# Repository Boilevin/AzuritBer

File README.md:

# AzuritBer
Ardumower full odometry version
see https://www.ardumower.de  and https://wiki.ardumower.de/index.php?title=AzuritBer_Firmware_(English)# for more info.

Master branch need PCB1.3 or 1.4 ,ODOMETRY on drive motor and IMU : GY-521 / or GY-88  based on MPU6050 version

OPTIONAL:

        	RFID BOARD PN5180 AS RFID READER and ESP32 dev kit to manage SPI communication with PN5180 and WIFI/BT for arduremote
	
		RASPBERRY for vision or camera streaming:
	
See other branch for GY-87  or MPU-9250/9255 version

GY87 version use a GY87 IMU connected on I2C1 to avoid i2c adress conflit with RTC .

RL1000 version is the code for robomow rl model platform.
	The 3 big mow motor use 3 BTS7960 motor driver and 3 INA226 with R010 instead R100 to manage motor sense over I2C

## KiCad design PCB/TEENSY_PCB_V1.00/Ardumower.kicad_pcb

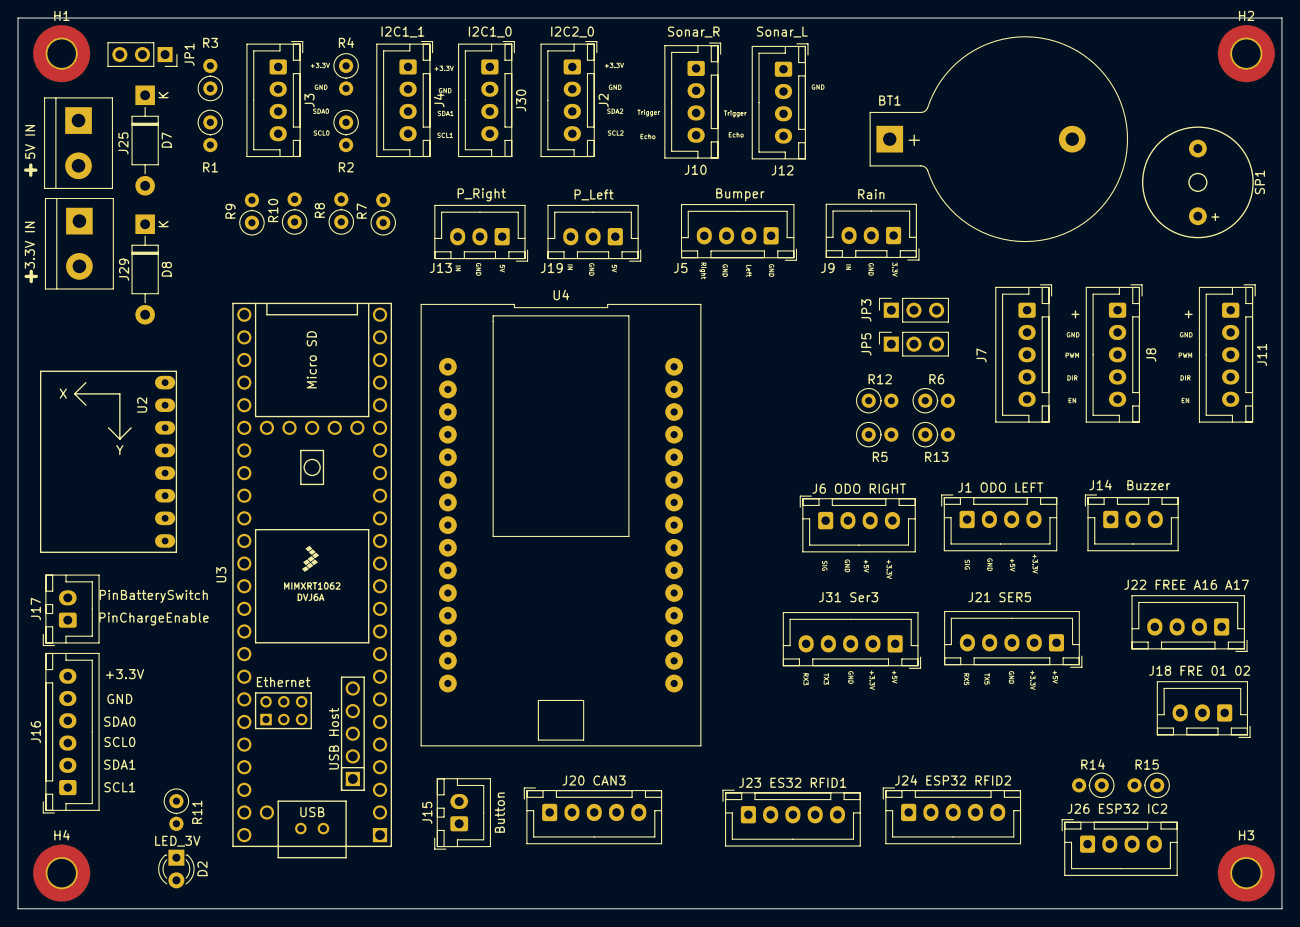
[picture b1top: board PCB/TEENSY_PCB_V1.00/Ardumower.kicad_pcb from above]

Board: 2 copper layers, 141.9 x 100.0 mm, 59 parts (0 on the bottom side), 66 nets, no tracks yet.

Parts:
BT1: Battery_Cell; BatteryHolder_Keystone_103_1x20mm
D2: LED_3V; LED_D3.0mm
D7, D8: 1N5819; D_DO-41_SOD81_P10.16mm_Horizontal
H1, H2, H3, H4: MountingHole_Pad; MountingHole_3.2mm_M3_Pad_TopBottom
J1 ODO LEFT: ODO_Left; JST_XH_B4B-XH-A_1x04_P2.50mm_Vertical
J2: I2C2_0; JST_XH_B4B-XH-A_1x04_P2.50mm_Vertical
J3: I2C0_0; JST_XH_B4B-XH-A_1x04_P2.50mm_Vertical
J4: I2C1_1; JST_XH_B4B-XH-A_1x04_P2.50mm_Vertical
J5: Bumper; JST_XH_B4B-XH-A_1x04_P2.50mm_Vertical
J6 ODO RIGHT: ODO_Right; JST_XH_B4B-XH-A_1x04_P2.50mm_Vertical
J7: Motor_Right1; JST_XH_B5B-XH-A_1x05_P2.50mm_Vertical
J8: Motor_Left1; JST_XH_B5B-XH-A_1x05_P2.50mm_Vertical
J9: Rain; JST_XH_B3B-XH-A_1x03_P2.50mm_Vertical
J10: Sonar_R; JST_XH_B4B-XH-A_1x04_P2.50mm_Vertical
J11: Cutter; JST_XH_B5B-XH-A_1x05_P2.50mm_Vertical
J12: Sonar_L; JST_XH_B4B-XH-A_1x04_P2.50mm_Vertical
J13: P_Right; JST_XH_B3B-XH-A_1x03_P2.50mm_Vertical
J14: Buzzer; JST_XH_B3B-XH-A_1x03_P2.50mm_Vertical
J15: Button; JST_XH_B2B-XH-A_1x02_P2.50mm_Vertical
J16: Power_PCB1; JST_XH_B6B-XH-A_1x06_P2.50mm_Vertical
J17: Power_PCB2; JST_XH_B2B-XH-A_1x02_P2.50mm_Vertical
J18 FRE 01 02: Free01_02; JST_XH_B3B-XH-A_1x03_P2.50mm_Vertical
J19: P_Left; JST_XH_B3B-XH-A_1x03_P2.50mm_Vertical
J20 CAN3: Can3; JST_XH_B5B-XH-A_1x05_P2.50mm_Vertical
J21 SER5: Ser5; JST_XH_B5B-XH-A_1x05_P2.50mm_Vertical
J22 FREE A16 A17: FreeA16_A17; JST_XH_B4B-XH-A_1x04_P2.50mm_Vertical
J23 ES32 RFID1: ESP RFID1; JST_XH_B5B-XH-A_1x05_P2.50mm_Vertical
J24 ESP32 RFID2: ESP RFID2; JST_XH_B5B-XH-A_1x05_P2.50mm_Vertical
J25: 5V IN; TerminalBlock_bornier-2_P5.08mm
J26 ESP32 IC2: ESP32 I2C; JST_XH_B4B-XH-A_1x04_P2.50mm_Vertical
J29: 3.3V IN; TerminalBlock_bornier-2_P5.08mm
J30: I2C1_0; JST_XH_B4B-XH-A_1x04_P2.50mm_Vertical
J31: Ser3; JST_XH_B5B-XH-A_1x05_P2.50mm_Vertical
JP1: Jumper_3.3V; PinSocket_1x03_P2.54mm_Vertical
JP3: MotorPower; PinSocket_1x03_P2.54mm_Vertical
JP5: CutterPower; PinSocket_1x03_P2.54mm_Vertical
R1, R3: XXXX; R_Axial_DIN0207_L6.3mm_D2.5mm_P2.54mm_Vertical
R2, R4, R14, R15: XXX; R_Axial_DIN0207_L6.3mm_D2.5mm_P2.54mm_Vertical
R5, R6, R7, R9: 1KO; R_Axial_DIN0207_L6.3mm_D2.5mm_P2.54mm_Vertical
R8, R10: 1.5KO; R_Axial_DIN0207_L6.3mm_D2.5mm_P2.54mm_Vertical
R11: 100; R_Axial_DIN0207_L6.3mm_D2.5mm_P2.54mm_Vertical
R12, R13: 1,5KO; R_Axial_DIN0207_L6.3mm_D2.5mm_P2.54mm_Vertical
SP1: SPEAKER; Buzzer_12x9.5RM7.6
U2: GY-521
U3: Teensy4.1; Teensy41
U4: ESP32-DEVKIT-V1

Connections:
+3V3: J1 ODO LEFT.4, J2.1, J3.1, J4.1, J6 ODO RIGHT.4, J9.1, J10.1, J12.1, J16.6, J20 CAN3.2, J21 SER5.2, J22 FREE A16 A17.1, J30.1, J31.2, JP1.2, JP3.3, JP5.3, R1.2, R2.2, R3.1, R4.2, R11.2, U2.1
+5V: D7.1, J1 ODO LEFT.3, J6 ODO RIGHT.3, J13.1, J14.1, J19.1, J20 CAN3.1, J21 SER5.1, J23 ES32 RFID1.2, J31.1, JP3.1, JP5.1, U3.48, U4.15
CRX3: J20 CAN3.5, U3.22
CTX3: J20 CAN3.4, U3.23
Free01: J18 FRE 01 02.2, U3.35
Free02: J18 FRE 01 02.3, U3.24
FreeA16: J22 FREE A16 A17.3, U3.32
FreeA17: J22 FREE A16 A17.4, U3.33
GND: BT1.2, D2.1, H1.1, H2.1, H3.1, H4.1, J1 ODO LEFT.2, J2.2, J3.2, J4.2, J5.1, J5.3, J6 ODO RIGHT.2, J7.2, J8.2, J9.2, J10.2, J11.2, J12.2, J13.2, J14.2, J15.1, J16.5, J18 FRE 01 02.1, J19.2, J20 CAN3.3, J21 SER5.3, J22 FREE A16 A17.2, J23 ES32 RFID1.1, J25.1, J26 ESP32 IC2.1, J29.1, J30.2, J31.3, R8.2, R10.2, R12.2, R13.2, SP1.1, U2.2, U3.47, U4.14
unnamed: BT1.1, U3.50
unnamed: D2.2, R11.1
unnamed: D7.2, J25.2
unnamed: D8.1, JP1.1
unnamed: D8.2, J29.2
unnamed: J1 ODO LEFT.1, R5.1, R12.1
unnamed: J6 ODO RIGHT.1, R6.1, R13.1
unnamed: J7.1, J8.1, JP3.2
unnamed: J11.1, JP5.2
unnamed: J13.3, R7.1, R8.1
unnamed: J19.3, R9.1, R10.1
unnamed: J23 ES32 RFID1.3, U4.13
unnamed: J23 ES32 RFID1.4, U4.12
unnamed: J23 ES32 RFID1.5, U4.11
unnamed: J24 ESP32 RFID2.1, U4.30
unnamed: J24 ESP32 RFID2.2, U4.25
unnamed: J24 ESP32 RFID2.3, U4.24
unnamed: J24 ESP32 RFID2.4, J26 ESP32 IC2.4, R14.1, R15.1, U4.16
unnamed: J26 ESP32 IC2.2, R14.2, U4.18
unnamed: J26 ESP32 IC2.3, R15.2, U4.20
unnamed: JP1.3, U3.46
RX1: U3.2, U4.22
RX3: J31.5, U3.37
RX5: J21 SER5.5, U3.43
SCL0: J3.4, J16.3, R1.1, U2.3, U3.41
SCL1: J4.4, J16.1, J30.4, R2.1, U3.38
SCL2: J2.4, U3.16
SDA0: J3.3, J16.4, R3.2, U2.4, U3.40
SDA1: J4.3, J16.2, J30.3, R4.1, U3.39
SDA2: J2.3, U3.17
TX1: U3.3, U4.21
TX3: J31.4, U3.36
TX5: J21 SER5.4, U3.42
pinBatterySwitch: J17.2, U3.25
pinBumperLeft: J5.4, U3.27
pinBumperRight: J5.2, U3.28
pinButton: J15.2, U3.30
pinBuzzer: J14.3, SP1.2, U3.29
pinChargeEnable: J17.1, U3.26
pinMotorLeftDir: J8.4, U3.8
pinMotorLeftEnable: J8.5, U3.7
pinMotorLeftPWM: J8.3, U3.9
pinMotorMowDir: J11.4, U3.11
pinMotorMowEnable: J11.5, U3.10
pinMotorMowPWM: J11.3, U3.12
pinMotorRightDir: J7.4, U3.5
pinMotorRightEnable: J7.5, U3.4
pinMotorRightPWM: J7.3, U3.6
pinOdometryLeft: R6.2, U3.14
pinOdometryRight: R5.2, U3.13
pinPerimeterLeft: R9.2, U3.45
pinPerimeterRight: R7.2, U3.44
pinRain: J9.3, U3.31
pinSonarLeftEcho: J12.4, U3.18
pinSonarLeftTrigger: J12.3, U3.20
pinSonarRightEcho: J10.4, U3.19
pinSonarRightTrigger: J10.3, U3.21

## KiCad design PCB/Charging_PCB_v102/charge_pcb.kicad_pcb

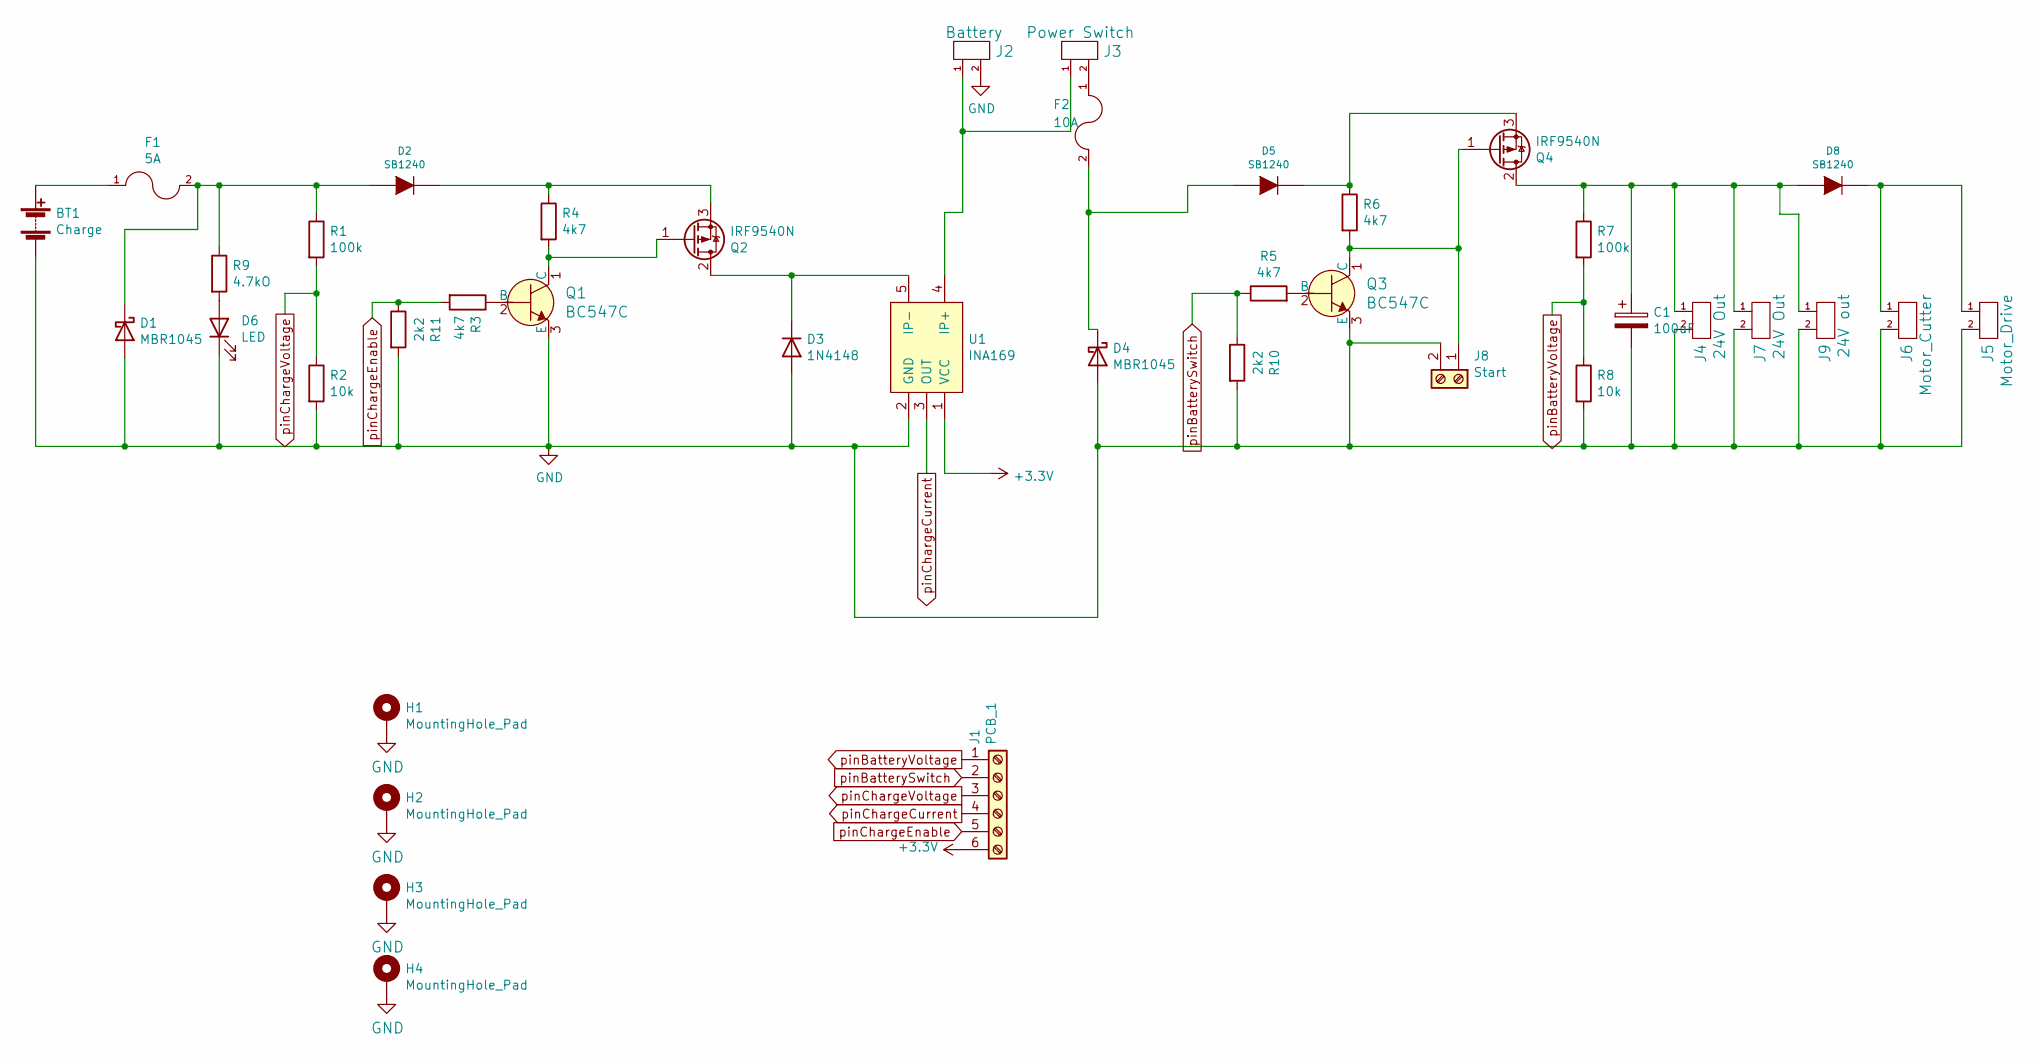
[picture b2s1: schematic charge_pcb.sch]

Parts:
BT1: Charge; Anschlussklemme_2P_RM5,08
C1: 100uF; Elko_vert_11.2x6.3mm_RM2.5
D1, D4: MBR1045; TO-220-2_Vertical
D2, D5, D8: SB1240; D_DO-41_SOD81_P10.16mm_Horizontal
D3: 1N4148; D_DO-35_SOD27_P7.62mm_Horizontal
D6: LED; LED_D1.8mm_W3.3mm_H2.4mm
F1: 5A; Fuseholder_Reichelt_PL112000
F2: 10A; Fuseholder_Reichelt_PL112000
H1, H2, H3, H4: MountingHole_Pad; MountingHole_3.2mm_M3_DIN965_Pad_TopBottom
J1: PCB_1; JST_XH_B6B-XH-A_1x06_P2.50mm_Vertical
J2: Battery; TerminalBlock_bornier-2_P5.08mm
J3: Power Switch; TerminalBlock_bornier-2_P5.08mm
J4, J7: 24V Out; TerminalBlock_bornier-2_P5.08mm
J5: Motor_Drive; TerminalBlock_bornier-2_P5.08mm
J6: Motor_Cutter; TerminalBlock_bornier-2_P5.08mm
J8: Start; JST_XH_B2B-XH-A_1x02_P2.50mm_Vertical
J9: 24V out; TerminalBlock_bornier-2_P5.08mm
Q1, Q3: BC547C; TO-92-3_Formed_Leads; MPN BC548BTA; Digi-Key_PN BC548BTACT-ND
Q2, Q4: IRF9540N; TO-220-3_Vertical
R1, R7: 100k; R_Axial_DIN0207_L6.3mm_D2.5mm_P7.62mm_Horizontal
R2, R8: 10k; R_Axial_DIN0207_L6.3mm_D2.5mm_P7.62mm_Horizontal
R3, R4, R5, R6: 4k7; R_Axial_DIN0207_L6.3mm_D2.5mm_P7.62mm_Horizontal
R9: 4.7kO; R_Axial_DIN0207_L6.3mm_D2.5mm_P7.62mm_Horizontal
R10, R11: 2k2; R_Axial_DIN0207_L6.3mm_D2.5mm_P7.62mm_Horizontal
U1: INA169; INA169_mit_Pinnummern

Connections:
+3V3: J1.6, U1.1 (VCC)
GND: BT1.2 (-), C1.2, D1.2 (A), D3.2 (A), D4.2 (A), D6.1 (K), H1.1, H2.1, H3.1, H4.1, J2.2, J4.2, J5.2, J6.2, J7.2, J8.2, J9.2, Q1.3 (E), Q3.3 (E), R2.2, R8.2, R10.2, R11.2, U1.2 (GND)
unnamed: BT1.1 (+), F1.1
unnamed: C1.1, D8.1 (A), J4.1, J7.1, J9.1, Q4.2 (D), R7.1
unnamed: D1.1 (K), D2.1 (A), F1.2, R1.1, R9.1
unnamed: D2.2 (K), Q2.3 (S), R4.1
unnamed: D3.1 (K), Q2.2 (D), U1.5 (IP-)
unnamed: D4.1 (K), D5.1 (A), F2.2
unnamed: D5.2 (K), Q4.3 (S), R6.1
unnamed: D6.2 (A), R9.2
unnamed: D8.2 (K), J5.1, J6.1
unnamed: F2.1, J3.2
unnamed: J2.1, J3.1, U1.4 (IP+)
unnamed: J8.1, Q3.1 (C), Q4.1 (G), R6.2
unnamed: Q1.1 (C), Q2.1 (G), R4.2
unnamed: Q1.2 (B), R3.1
unnamed: Q3.2 (B), R5.2
pinBatterySwitch: J1.2, R5.1, R10.1
pinBatteryVoltage: J1.1, R7.2, R8.1
pinChargeCurrent: J1.4, U1.3 (OUT)
pinChargeEnable: J1.5, R3.2, R11.1
pinChargeVoltage: J1.3, R1.2, R2.1

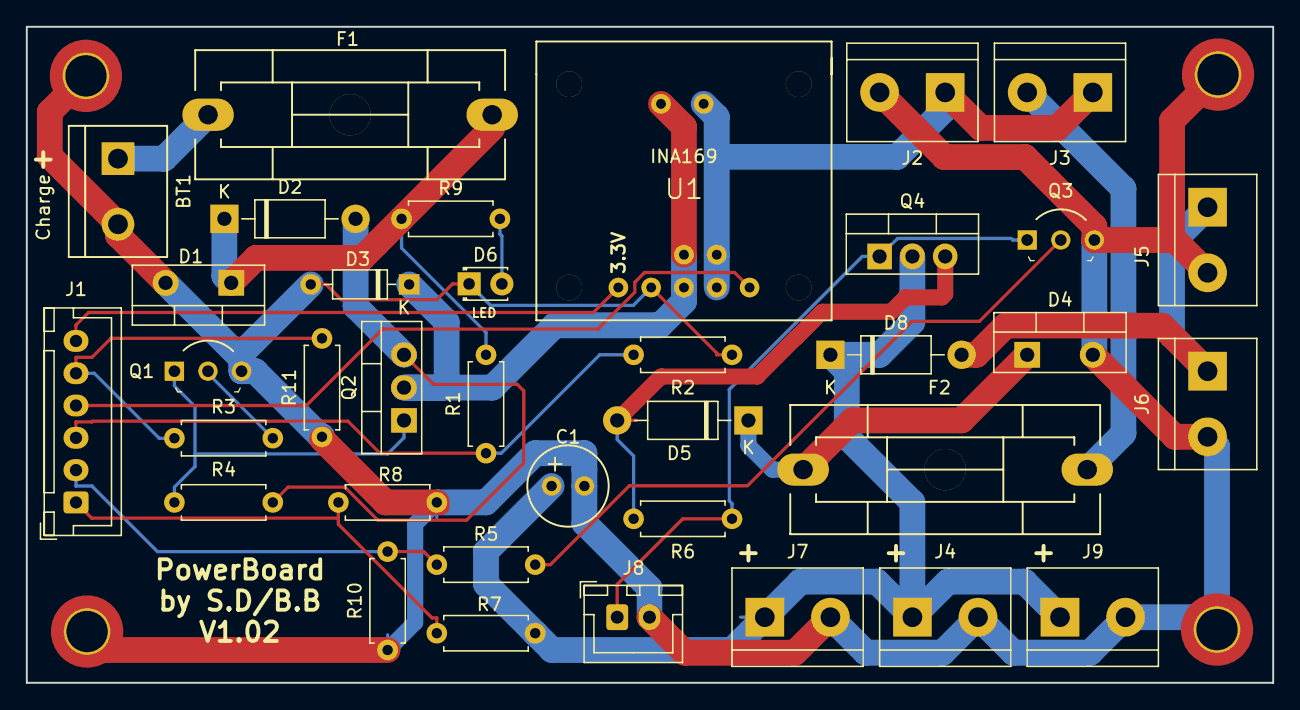
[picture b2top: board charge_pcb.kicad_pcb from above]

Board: 2 copper layers, 96.5 x 50.8 mm, 40 parts (0 on the bottom side), 22 nets.

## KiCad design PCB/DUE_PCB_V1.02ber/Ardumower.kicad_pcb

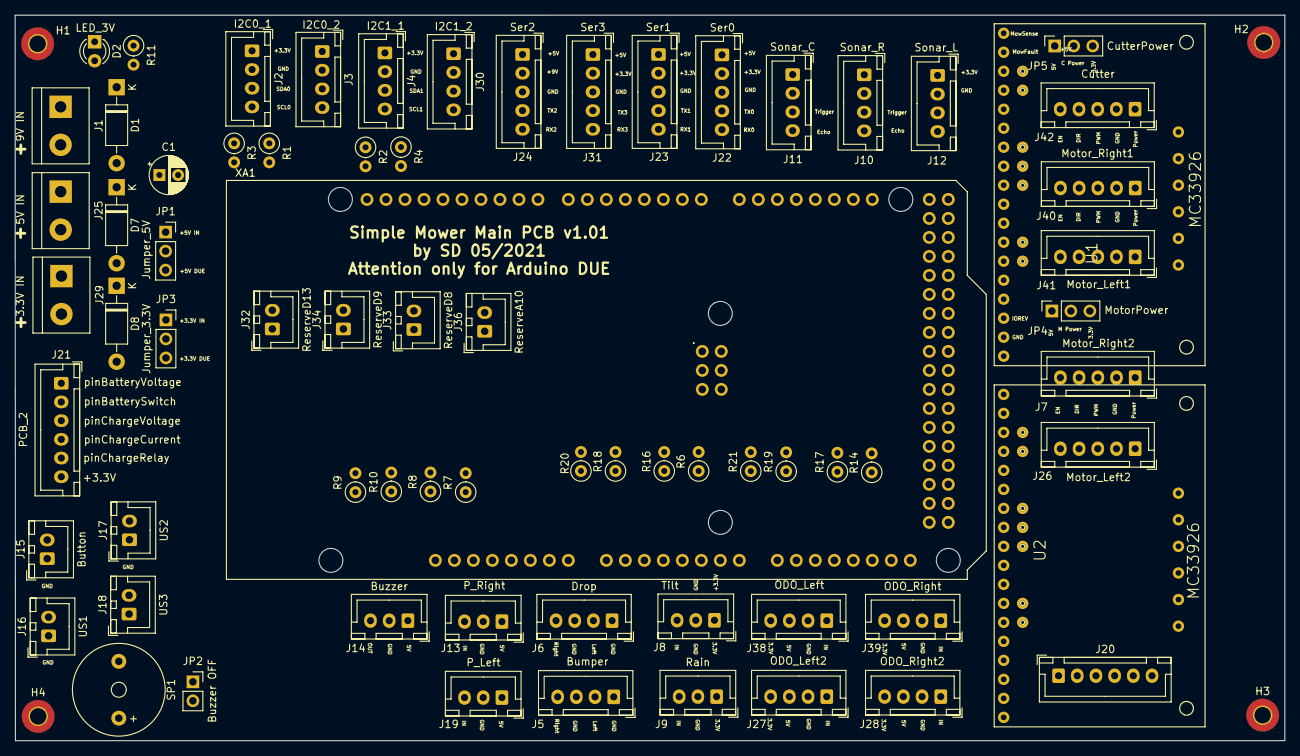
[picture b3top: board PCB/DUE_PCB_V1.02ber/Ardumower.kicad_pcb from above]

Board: 2 copper layers, 169.8 x 97.0 mm, 75 parts (0 on the bottom side), 93 nets, no tracks yet.

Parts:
C1: 100nF; CP_Radial_D5.0mm_P2.50mm
D1, D7, D8: 1N5819; D_DO-41_SOD81_P10.16mm_Horizontal
D2: LED_3V; LED_D3.0mm
H1, H2, H3, H4: MountingHole_Pad; MountingHole_2.2mm_M2_Pad_TopBottom
J1: 9V IN; TerminalBlock_bornier-2_P5.08mm
J2: I2C0_1; JST_XH_B4B-XH-A_1x04_P2.50mm_Vertical
J3: I2C0_2; JST_XH_B4B-XH-A_1x04_P2.50mm_Vertical
J4: I2C1_1; JST_XH_B4B-XH-A_1x04_P2.50mm_Vertical
J5: Bumper; JST_XH_B4B-XH-A_1x04_P2.50mm_Vertical
J6: Drop; JST_XH_B4B-XH-A_1x04_P2.50mm_Vertical
J7: Motor_Right2; JST_XH_B5B-XH-A_1x05_P2.50mm_Vertical
J8: Tilt; JST_XH_B3B-XH-A_1x03_P2.50mm_Vertical
J9: Rain; JST_XH_B3B-XH-A_1x03_P2.50mm_Vertical
J10: Sonar_R; JST_XH_B4B-XH-A_1x04_P2.50mm_Vertical
J11: Sonar_C; JST_XH_B4B-XH-A_1x04_P2.50mm_Vertical
J12: Sonar_L; JST_XH_B4B-XH-A_1x04_P2.50mm_Vertical
J13: P_Right; JST_XH_B3B-XH-A_1x03_P2.50mm_Vertical
J14: Buzzer; JST_XH_B3B-XH-A_1x03_P2.50mm_Vertical
J15: Button; JST_XH_B2B-XH-A_1x02_P2.50mm_Vertical
J16: US1; JST_XH_B2B-XH-A_1x02_P2.50mm_Vertical
J17: US2; JST_XH_B2B-XH-A_1x02_P2.50mm_Vertical
J18: US3; JST_XH_B2B-XH-A_1x02_P2.50mm_Vertical
J19: P_Left; JST_XH_B3B-XH-A_1x03_P2.50mm_Vertical
J20: UserOut; JST_XH_B6B-XH-A_1x06_P2.50mm_Vertical
J21: PCB_2; JST_XH_B6B-XH-A_1x06_P2.50mm_Vertical
J22: Ser0; JST_XH_B5B-XH-A_1x05_P2.50mm_Vertical
J23: Ser1; JST_XH_B5B-XH-A_1x05_P2.50mm_Vertical
J24: Ser2; JST_XH_B5B-XH-A_1x05_P2.50mm_Vertical
J25: 5V IN; TerminalBlock_bornier-2_P5.08mm
J26: Motor_Left2; JST_XH_B5B-XH-A_1x05_P2.50mm_Vertical
J27: ODO_Left2; JST_XH_B4B-XH-A_1x04_P2.50mm_Vertical
J28: ODO_Right2; JST_XH_B4B-XH-A_1x04_P2.50mm_Vertical
J29: 3.3V IN; TerminalBlock_bornier-2_P5.08mm
J30: I2C1_2; JST_XH_B4B-XH-A_1x04_P2.50mm_Vertical
J31: Ser3; JST_XH_B5B-XH-A_1x05_P2.50mm_Vertical
J32: ReserveD13; JST_XH_B2B-XH-A_1x02_P2.50mm_Vertical
J33: ReserveD8; JST_XH_B2B-XH-A_1x02_P2.50mm_Vertical
J34: ReserveD9; JST_XH_B2B-XH-A_1x02_P2.50mm_Vertical
J36: ReserveA10; JST_XH_B2B-XH-A_1x02_P2.50mm_Vertical
J38: ODO_Left; JST_XH_B4B-XH-A_1x04_P2.50mm_Vertical
J39: ODO_Right; JST_XH_B4B-XH-A_1x04_P2.50mm_Vertical
J40: Motor_Right1; JST_XH_B5B-XH-A_1x05_P2.50mm_Vertical
J41: Motor_Left1; JST_XH_B5B-XH-A_1x05_P2.50mm_Vertical
J42: Cutter; JST_XH_B5B-XH-A_1x05_P2.50mm_Vertical
JP1: Jumper_5V; PinSocket_1x03_P2.54mm_Vertical
JP2: Buzzer OFF; PinSocket_1x02_P2.54mm_Vertical
JP3: Jumper_3.3V; PinSocket_1x03_P2.54mm_Vertical
JP4: MotorPower; PinSocket_1x03_P2.54mm_Vertical
JP5: CutterPower; PinSocket_1x03_P2.54mm_Vertical
R1, R2, R3, R4: XXX; R_Axial_DIN0207_L6.3mm_D2.5mm_P2.54mm_Vertical
R6, R7, R9, R14, R18, R19: 1KO; R_Axial_DIN0207_L6.3mm_D2.5mm_P2.54mm_Vertical
R8, R10: 1.5KO; R_Axial_DIN0207_L6.3mm_D2.5mm_P2.54mm_Vertical
R11: 100; R_Axial_DIN0207_L6.3mm_D2.5mm_P2.54mm_Vertical
R16, R17, R20, R21: 1,5KO; R_Axial_DIN0207_L6.3mm_D2.5mm_P2.54mm_Vertical
SP1: SPEAKER; Buzzer_12x9.5RM7.6
U1, U2: MC33926; MC_33926_31polig_mit_Bohrloch_neue_Masse
XA1: Arduino_Due_Shield

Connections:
+3V3: J2.1, J3.1, J4.1, J8.1, J9.1, J10.1, J11.1, J12.1, J20.2, J21.6, J22.2, J23.2, J27.4, J28.4, J30.1, J31.2, J38.4, J39.4, JP3.2, JP4.3, JP5.3, R1.2, R2.2, R3.2, R4.2
+5V: J13.1, J14.1, J19.1, J22.1, J23.1, J24.1, J27.3, J28.3, J31.1, J38.3, J39.3, JP1.2, JP4.1, JP5.1
+9V: D1.1, J24.2, XA1.VIN
DUE_3.3V: JP3.3, R11.2, XA1.3V3
DUE_5V: JP1.3, XA1.5V1
GND: C1.1, D2.1, H1.1, H2.1, H3.1, H4.1, J1.1, J2.2, J3.2, J4.2, J5.1, J5.3, J6.1, J6.3, J7.2, J8.2, J9.2, J10.2, J11.2, J12.2, J13.2, J14.2, J15.1, J16.1, J17.1, J18.1, J19.2, J20.1, J22.3, J23.3, J24.3, J25.1, J26.2, J27.2, J28.2, J29.1, J30.2, J31.3, J32.1, J33.1, J34.1, J36.1, J38.2, J39.2, J40.2, J41.2, J42.2, R8.2, R10.2, R16.2, R17.2, R20.2, R21.2, SP1.1, U1.2, U1.7, U1.16, U2.2, U2.7, U2.16, XA1.GND1, XA1.GND2, XA1.GND3, XA1.GND5, XA1.GND6
IOREV: U1.3, U1.6, U1.15, U2.3, U2.6, U2.15, XA1.IORF
unnamed: C1.2, XA1.AREF
unnamed: D1.2, J1.2
unnamed: D2.2, R11.1
unnamed: D7.1, JP1.1
unnamed: D7.2, J25.2
unnamed: D8.1, JP3.1
unnamed: D8.2, J29.2
unnamed: J13.3, R7.1, R8.1
unnamed: J19.3, R9.1, R10.1
unnamed: J7.1, J26.1, J40.1, J41.1, JP4.2
unnamed: J27.1, R18.1, R20.1
unnamed: J28.1, R19.1, R21.1
unnamed: J38.1, R6.1, R16.1
unnamed: J39.1, R14.1, R17.1
unnamed: J42.1, JP5.2
unnamed: JP2.2, SP1.2
RX0: J22.5, XA1.D0
RX1: J23.5, XA1.D19
RX2: J24.5, XA1.D17
RX3: J31.5, XA1.D14
SCL0: J2.4, J3.4, R1.1, XA1.D21
SCL1: J4.4, J30.4, R2.1, XA1.SCL1
SDA0: J2.3, J3.3, R3.1, XA1.D20
SDA1: J4.3, J30.3, R4.1, XA1.SDA1
TX0: J22.4, XA1.D1
TX1: J23.4, XA1.D18
TX2: J24.4, XA1.D16
TX3: J31.4, XA1.D15
pinBatterySwitch: J21.2, XA1.D4
pinBatteryVoltage: J21.1, XA1.A2
pinBumperLeft: J5.4, XA1.D39
pinBumperRight: J5.2, XA1.D38
pinButton: J15.2, XA1.D51
pinBuzzer: J14.3, JP2.1, XA1.D53
pinChargeCurrent: J21.4, XA1.A8
pinChargeEnable: J21.5, XA1.D50
pinChargeVoltage: J21.3, XA1.A9
pinDropLeft: J6.4, XA1.D45
pinDropRight: J6.2, XA1.D23
pinMotorEnable: J40.5, U2.10, XA1.D37
pinMotorLeft2Dir: J26.4, XA1.D40
pinMotorLeft2Enable: J26.5, XA1.D42
pinMotorLeft2PWM: J26.3, XA1.D6
pinMotorLeftDir: J41.4, U2.4, XA1.D31
pinMotorLeftEnable: J41.5, XA1.D49
pinMotorLeftFault: U2.8, XA1.D25
pinMotorLeftPWM: J41.3, U2.5, XA1.D5
pinMotorLeftSense: U2.9, XA1.A1
pinMotorMow1Sense: U1.9, XA1.A6
pinMotorMowDir: J42.4, U1.4, U1.13, XA1.D29
pinMotorMowEnable: J42.5, U1.10, XA1.D28
pinMotorMowFault: U1.8, U1.17, XA1.D26
pinMotorMowPWM: J42.3, U1.5, U1.14, XA1.D2
pinMotorMowSense: U1.18, XA1.A3
pinMotorRight2Dir: J7.4, XA1.D41
pinMotorRight2Enable: J7.5, XA1.D43
pinMotorRight2PWM: J7.3, XA1.D7
pinMotorRightDir: J40.4, U2.13, XA1.D33
pinMotorRightFault: U2.17, XA1.D27
pinMotorRightPWM: J40.3, U2.14, XA1.D3
pinMotorRightSense: U2.18, XA1.A0
pinOdometryLeft: R14.2, XA1.DAC0
pinOdometryLeft2: R19.2, XA1.DAC1
pinOdometryRight: R6.2, XA1.CANR
pinOdometryRight2: R18.2, XA1.CANT
pinPerimeterLeft: R9.2, XA1.A5
pinPerimeterRight: R7.2, XA1.A4
pinRain: J9.3, XA1.D44
pinReserveA10: J36.2, XA1.A10
pinReserveD8: J33.2, XA1.D8
pinReserveD9: J34.2, XA1.D9
pinReserveD13: J32.2, XA1.D13
pinSonarCenterEcho: J11.4, XA1.D22
pinSonarCenterTrigger: J11.3, XA1.D24
pinSonarLeftEcho: J12.4, XA1.D36
pinSonarLeftTrigger: J12.3, XA1.D34
pinSonarRightEcho: J10.4, XA1.D32
pinSonarRightTrigger: J10.3, XA1.D30
pinTilt: J8.3, XA1.D35
pinUserOut1: J20.3, XA1.D10
pinUserOut2: J20.4, XA1.D11
pinUserOut3: J20.5, XA1.D12
pinUserOut4: J20.6, XA1.D52
pinUserSwitch1: J16.2, XA1.D46
pinUserSwitch2: J17.2, XA1.D47
pinUserSwitch3: J18.2, XA1.D48

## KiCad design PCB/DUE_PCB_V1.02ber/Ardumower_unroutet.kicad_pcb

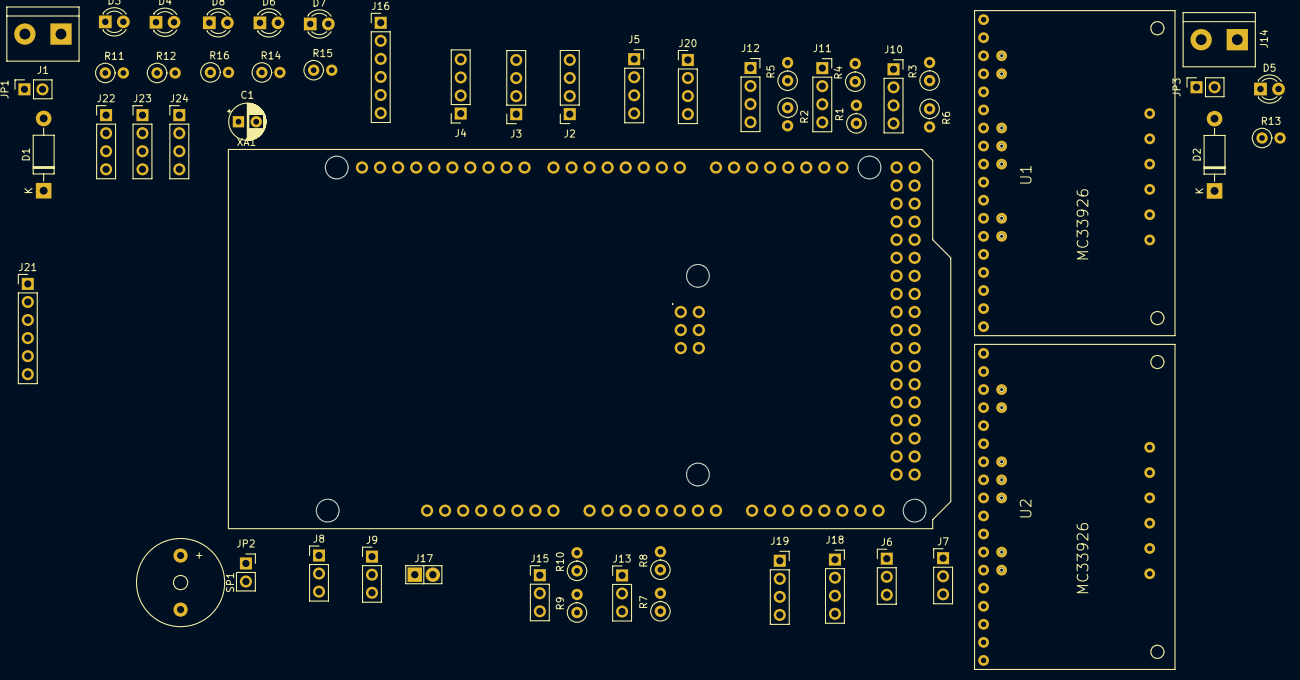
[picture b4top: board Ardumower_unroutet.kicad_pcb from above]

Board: 2 copper layers, 56 parts (0 on the bottom side), 78 nets, no tracks yet.

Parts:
C1: 100nF; CP_Radial_D5.0mm_P2.50mm
D1, D2: 1N5819; D_DO-41_SOD81_P10.16mm_Horizontal
D3: LED_3V; LED_D3.0mm
D4: LED_5V; LED_D3.0mm
D5: LED_24V; LED_D3.0mm
D6: LED; LED_D3.0mm
D7: LED_Green; LED_D3.0mm
D8: LED_Red; LED_D3.0mm
J1: 9V IN; TerminalBlock_bornier-2_P5.08mm
J2: I2C_1; PinSocket_1x04_P2.54mm_Vertical
J3: I2C_2; PinSocket_1x04_P2.54mm_Vertical
J4: I2C_3; PinSocket_1x04_P2.54mm_Vertical
J5: Bumper; PinSocket_1x04_P2.54mm_Vertical
J6: Drop_Left; PinHeader_1x03_P2.54mm_Vertical
J7: Drop_Right; PinHeader_1x03_P2.54mm_Vertical
J8: Tilt; PinHeader_1x03_P2.54mm_Vertical
J9: Rain; PinHeader_1x03_P2.54mm_Vertical
J10: Sonar_R; PinSocket_1x04_P2.54mm_Vertical
J11: Sonar_C; PinSocket_1x04_P2.54mm_Vertical
J12: Sonar_L; PinSocket_1x04_P2.54mm_Vertical
J13: P_Right; PinHeader_1x03_P2.54mm_Vertical
J14: 24V IN; TerminalBlock_bornier-2_P5.08mm
J15: P_Left; PinHeader_1x03_P2.54mm_Vertical
J16: DS3231 RTC; PinHeader_1x06_P2.54mm_Vertical
J17: Button; Pin_Header_KK110_1x02_3D
J18: ODO_Right; PinSocket_1x04_P2.54mm_Vertical
J19: ODO_Left; PinSocket_1x04_P2.54mm_Vertical
J20: Remote; PinHeader_1x04_P2.54mm_Vertical
J21: PCB_2; PinHeader_1x06_P2.54mm_Vertical
J22: 3.3V; PinHeader_1x04_P2.54mm_Vertical
J23: GND; PinHeader_1x04_P2.54mm_Vertical
J24: RX & TX; PinHeader_1x04_P2.54mm_Vertical
JP1: 9V; PinSocket_1x02_P2.54mm_Vertical
JP2: Buzzer OFF; PinSocket_1x02_P2.54mm_Vertical
JP3: 24V; PinSocket_1x02_P2.54mm_Vertical
R1, R2, R3, R7, R9: 1KO; R_Axial_DIN0207_L6.3mm_D2.5mm_P2.54mm_Vertical
R4, R5, R6: 2KO; R_Axial_DIN0207_L6.3mm_D2.5mm_P2.54mm_Vertical
R8, R10: 1.5KO; R_Axial_DIN0207_L6.3mm_D2.5mm_P2.54mm_Vertical
R11, R14, R15, R16: 100; R_Axial_DIN0207_L6.3mm_D2.5mm_P2.54mm_Vertical
R12: 220; R_Axial_DIN0207_L6.3mm_D2.5mm_P2.54mm_Vertical
R13: 1K5; R_Axial_DIN0207_L6.3mm_D2.5mm_P2.54mm_Vertical
SP1: SPEAKER; Buzzer_12x9.5RM7.6
U1, U2: MC33926; MC_33926_31polig_mit_Bohrloch_neue_Masse
XA1: Arduino_Due_Shield

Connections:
+3V3: J2.1, J3.1, J4.1, J6.1, J7.1, J8.1, J9.1, J16.5, J22.1, J22.2, J22.3, J22.4, R11.2, XA1.3V3
+5V: J10.1, J11.1, J12.1, J13.1, J15.1, J18.1, J19.1, R12.2, XA1.5V1
+9V: D1.1, XA1.VIN
+24V: D2.1, R13.2, U1.22, U2.22
GND: C1.1, D3.1, D4.1, D5.1, D6.1, D7.1, D8.1, J1.1, J2.2, J3.2, J4.2, J5.1, J5.3, J6.2, J7.2, J8.2, J9.2, J10.2, J11.2, J12.2, J13.2, J14.1, J15.2, J16.6, J17.1, J18.2, J19.2, J23.1, J23.2, J23.3, J23.4, R4.2, R5.2, R6.2, R8.2, R10.2, SP1.1, U1.2, U1.7, U1.16, U1.21, U2.2, U2.7, U2.16, U2.21, XA1.GND1, XA1.GND2, XA1.GND3, XA1.GND5, XA1.GND6
IOREV: U1.3, U1.6, U1.9, U1.15, U2.3, U2.6, U2.15, XA1.IORF
unnamed: C1.2, XA1.AREF
unnamed: D1.2, JP1.2
unnamed: D2.2, JP3.2
unnamed: D3.2, R11.1
unnamed: D4.2, R12.1
unnamed: D5.2, R13.1
unnamed: D6.2, R14.2
unnamed: D7.2, R15.2
unnamed: D8.2, R16.2
unnamed: J1.2, JP1.1
unnamed: J10.3, R3.1, R6.1
unnamed: J11.3, R1.1, R4.1
unnamed: J12.3, R2.1, R5.1
unnamed: J13.3, R7.1, R8.1
unnamed: J14.2, JP3.1
unnamed: J15.3, R9.1, R10.1
unnamed: JP2.2, SP1.2
RX1: J24.2, XA1.D19
RX2: J24.4, XA1.D17
SCL0: J2.4, J3.4, XA1.D21
SCL1: J4.4, J16.3, XA1.SCL1
SDA0: J2.3, J3.3, XA1.D20
SDA1: J4.3, J16.4, XA1.SDA1
TX1: J24.1, XA1.D18
TX2: J24.3, XA1.D16
pinBatterySwitch: J21.2, XA1.D4
pinBatteryVoltage: J21.1, XA1.A2
pinBumperLeft: J5.4, XA1.D39
pinBumperRight: J5.2, XA1.D38
pinButton: J17.2, XA1.D51
pinBuzzer: JP2.1, XA1.D53
pinChargeCurrent: J21.4, XA1.A8
pinChargeRelay: J21.5, XA1.D50
pinChargeVoltage: J21.3, XA1.A9
pinDropLeft: J6.3, XA1.D45
pinDropRight: J7.3, XA1.D23
pinGreenLED: R15.1, XA1.D6
pinLED: R14.1, XA1.D13
pinMotorEnable: U2.10, XA1.D37
pinMotorLeftDir: U2.4, XA1.D31
pinMotorLeftFault: U2.8, XA1.D25
pinMotorLeftPWM: U2.5, XA1.D5
pinMotorLeftSense: U2.9, XA1.A1
pinMotorMowDir: U1.4, U1.13, XA1.D29
pinMotorMowEnable: U1.10, XA1.D28
pinMotorMowFault: U1.8, U1.17, XA1.D26
pinMotorMowPWM: U1.5, U1.14, XA1.D2
pinMotorMowSense: U1.18, XA1.A3
pinMotorRightDir: U2.13, XA1.D33
pinMotorRightFault: U2.17, XA1.D27
pinMotorRightPWM: U2.14, XA1.D3
pinMotorRightSense: U2.18, XA1.A0
pinOdometryLeft: J19.3, XA1.DAC0
pinOdometryLeft2: J19.4, XA1.DAC1
pinOdometryRight: J18.3, XA1.CANR
pinOdometryRight2: J18.4, XA1.CANT
pinPerimeterLeft: R9.2, XA1.A5
pinPerimeterRight: R7.2, XA1.A4
pinRain: J9.3, XA1.D44
pinRedLED: R16.1, XA1.D7
pinRemoteMow: J20.3, XA1.D12
pinRemoteSpeed: J20.1, XA1.D10
pinRemoteSteer: J20.2, XA1.D11
pinRemoteSwitch: J20.4, XA1.D52
pinSonarCenterEcho: J11.4, XA1.D22
pinSonarCenterTrigger: R1.2, XA1.D24
pinSonarLeftEcho: J12.4, XA1.D36
pinSonarLeftTrigger: R2.2, XA1.D34
pinSonarRightEcho: J10.4, XA1.D32
pinSonarRightTrigger: R3.2, XA1.D30
pinTilt: J8.3, XA1.D35
pinVoltageMeasurement: J21.6, XA1.A7

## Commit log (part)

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2020-04-16 txt file
2020-04-17 mqtt
2020-04-17 factory var
2020-04-24 small screen Pi zero
2020-04-25 pyardu303
2020-04-28 v305
    Auto reconnection on WIFI lost with Jussip code parts
2020-05-05 watchdog timeout
2020-05-05 Create PiArdu312.py
    add the force to station if weather is bad
2020-05-07 test
2020-05-07 bug detect by jussip
2020-05-08 increase watchdog
    pi zero in wifi is low speed
2020-05-08 mqtt more stable
2020-05-09 cleaning
2020-05-10 new file for 3.5inch
2020-05-10 Sender update
2020-05-12 heltec
2020-05-12 f3d file again ?
2020-05-13 pi zero 3d
2020-05-13 mqtt addon
2020-05-13 piardu319
2020-05-14 bug in starttimer
2020-05-16 minor bug
2020-05-16 home assistant addon
2020-05-17 restart initiate by Pi
2020-05-17 Working code
    Error in Mowpattern start from 0 not 1
2020-05-17 first test
2020-05-17 filter pitch
2020-05-18 wire1 issue
2020-05-18 cleanning
2020-05-20 directory change
2020-05-21 more wire detection
2020-05-23 initial start
2020-05-23 bug on mowpattern
    Jussip bug detection
2020-05-25 brace missing
    Jussip detection
2020-05-26 motor power on track
2020-05-29 Low accelerate on startup
2020-06-07 Update pfod.cpp
    remove "rx" because same as h04 already use
2020-06-07 update from rfid branch
2020-06-11 mower.sh
2020-06-11 Update pfod.cpp
    allow save setting when charge
2020-06-14 ardu323
    Solve bug into day of week timer
    more err info in traceback
2020-06-14 v1.3
    prepare station setting.
2020-06-15 Imu Plot
    Add IMU plot not finish on the graphic KST build
2020-06-16 bool change and compass
    On compass bad calib the mower now start to mow in random
2020-06-17 freeze issue
    freeze issue on pyardu maybe problem in set time date
2020-06-18 Update RpiRemote.cpp
    Do nothing
2020-06-18 compass calibration
    When auto calibration fail the mower continue to mow in random mode
2020-06-21 Update robot.cpp
    mow motor restart after bad calib
2020-06-22 Update robot.cpp
    mow motor restart on bad calib
2020-06-23 ip fixe
    Sender use now IP FIX
2020-06-23 Update robot.cpp
    rolldir
2020-06-24 Update setup raspberry.rtf
    arduino ide setup on pi
2020-06-27 restore OTA Due
    Need to add switch on JP8 for flashing Due from Pi
2020-07-03 unixformat
2020-08-11 variable mow speed
    The mow motor speed is regulate using the hig of grass
2020-08-16 plot adjust
2020-08-16 Update robot.cpp
    add bumper and current test
2020-08-16 test with pc
2020-08-17 Update pfod.cpp
    reset timer from OFF
2020-08-18 timer
2020-08-18 Update mower.cpp
    factory setting odo
2020-08-22 off_reset_timer
2020-08-22 helper addon
2020-08-25 clean
2020-08-29 watchdog on imu
2020-08-31 2 loops build
2020-09-05 sender
2020-09-05 sender on piardu
2020-09-06 area 3 update
2020-09-10 temp issue
2020-09-10 waitsig2 easy trig
2020-09-12 GY87
2020-09-13 compassuse
2020-09-13 compassuse1
2020-09-13 nocompass
2020-09-13 compassuse2
2020-09-15 AREA3 SIGCODE
2020-09-17 overheat
    not tested
2020-09-17 init01
2020-09-17 step1
2020-09-18 first change
2020-09-18 clean1
2020-09-19 test rate
2020-09-20 test2
2020-09-20 compass fail
2020-09-25 Revert "compass fail"
    This reverts commit e49fa2d8beebfa4386e0630d3fc0de689e9c6a33.
2020-09-25 Revert "Revert "compass fail""
    This reverts commit f6b32a53e34359a12542c1e88b28cd669d32fbfb.
2020-09-25 Revert "Update imu.cpp"
    This reverts commit 31486dfd56871c4f2282a6e192cfbebbf7b68b52.
2020-09-25 Revert "test2"
    This reverts commit b9c0f9e9a7465d96cf3632009acbfaf5e3c44473.
2020-09-25 Revert "test rate"
    This reverts commit 36f93036a201f1b0b6f0c9336d5934a5f290cfd4.
2020-09-25 Revert "Update imu.cpp"
    This reverts commit 7122ba7de01ac4edba1df3d4b09fa150cb42ebc0.
2020-09-26 compass calib not ok
2020-09-27 compass calib
2020-09-28 Revert "Update imu.cpp"
    This reverts commit c5afb98bc38f7f65467262f8e3db21e3e4c6c8f9.
2020-09-28 Revert "Update imu.cpp"
    This reverts commit 349867b6922ddae2e5dbccb1d251185f6e663e92.
2020-09-28 revert
2020-09-29 stage2
2020-10-02 test5
2020-10-04 running test with compass
2020-10-04 rebuild all
2020-10-07 deactivate PI and compass
    For standard use
2020-10-07 menu help
2020-10-18 simple
2020-10-24 Revert "overheat"
    This reverts commit e70847e190c874d842470f47cfe79bc57c8f6771.
2020-10-24 redled
2020-10-24 led2
2020-10-25 led5
2020-10-25 mqtt freeze
2020-10-26 3d file move
2020-10-30 pfod3
2020-11-06 mqtt
    mqtt loop change mode
2020-11-09 Update robot.cpp
    More robust tracking
2020-11-09 Update robot.cpp
    More robust tracking on wet grass
2020-11-11 ESP8266 activation
    Reset the GPS to his original port
2020-11-14 esp8266 support
2020-11-19 info
2020-11-20 imu i2c reset
    After a long Duration MPU-9255 freeze i2c bus
2020-11-22 Update perimeter.cpp
    sigcade area3
2020-11-22 new piardu
2020-11-23 add rfid board easyeda
2020-12-01 f3d file
    clean fusion 360 file
2020-12-02 gps speed
2020-12-16 3dfile
2020-12-16 piardu vision test
2020-12-17 vision2
2020-12-27 vision 2
2021-01-25 Update RpiRemote.cpp
    date time not save from piardu to due
2021-01-25 Update RpiRemote.cpp
    datetime from pi
2021-01-25 Update RpiRemote.cpp
    datetime update
2021-02-06 add vision
2021-02-07 userout correction
2021-02-13 relay adjust
2021-02-14 relay out
2021-02-20 mow pwm
2021-03-06 reverse vision avoid
2021-03-07 vision as bumper
2021-03-09 start button management
2021-03-09 wire mowing obstacle
2021-03-11 vision file
2021-03-12 new button soft
2021-03-14 big bat charge
2021-03-15 button issue
2021-03-19 blink led
2021-03-23 halflane
    In bylane mowing the spirale is not a good idea.
    Better only one rot 360 and reduce de distance between lane for the next 3 lane
2021-03-25 sonar vs speed
    reduce speed on sonar or bumper like
    setting possible into arduremote
2021-03-25 sonar to pi
2021-03-26 autoBylaneToRandom
    When mower reach a corner in bylane it's possible to change to random mode
2021-03-27 blink led sender
2021-03-27 button behaviour
2021-03-27 p20 button
2021-03-27 Auto bylane to random
2021-03-28 speed on roll
2021-03-28 sonar speed
    Possible to change sonar behaviour and only reduce speed vs act like a bumper
2021-04-02 QMC5883 compass
2021-04-03 esp8266 tested
2021-04-03 area2 sender
2021-04-03 multiple area new sender 2 loops
2021-04-04 new compass code
    GY-273 using QMC5883L OK
2021-04-05 perimeterspeedcoeff
    reduce speed near perimeter
2021-04-06 v521
2021-04-07 vision version
2021-04-10 IMU on I2C1
2021-04-10 mpu-9250- on i2c1
2021-04-10 ERASE
2021-04-11 rename version
2021-04-11 test reset imu
2021-04-12 bug in plot imu
2021-04-14 imu reading duration
    Check imu reading duration
2021-04-17 rpm auto set
2021-04-17 auto rpm set
2021-04-18 autoAdjustSlopeSpeed
    autoAdjustSlopeSpeed
2021-04-20 reduce speed near perimeter
2021-04-20 escape island
    no rfid escape island
2021-04-20 stuck on island
    if no rfid use 6 full right rev
2021-04-24 random speed rpm
2021-04-24 Imu tilt continue to mow
2021-04-25 track CCW
2021-04-29 spirale bumper issue
2021-04-29 spirale bumper
    stop faster when bumper on spirale mowing
2021-05-01 sonar test
2021-05-16 DS3231 RTC
2021-05-24 Charge PCB
    Here the v1.01
2021-05-24 Update pfod.cpp
    compatibility with arduremote
2021-05-30 pcb working
2021-05-30 Update robot.cpp
    sonar change code
2021-06-02 Second Perimeter Coil
2021-06-06 1.02ver
2021-06-12 poweroff
    poweroff if manaul
    perifind heading on obstacle
2021-06-12 poweroff
    poweroff if manual
    correct heading after periobstacle
2021-06-17 ROLL DIR IN CCW TRACKING
2021-06-18 piardu v525
2021-06-20 pfod console
2021-06-21 oled 128 64
2021-06-21 mowpattern change
2021-06-22 screen 001
2021-06-24 screen 002
    test speed
2021-06-27 screen 003
2021-06-30 u8x8 version
    U8x8 is faster and manage the SSH1106
2021-06-30 start button into station
2021-07-06 teensy pcb
2021-07-06 rolldir restore
2021-07-08 gy521 test
2021-07-14 preversion
2021-07-14 power route
2021-07-22 ordered teensy pcb
2021-07-24 u8g2
2021-07-24 screen
2021-07-25 display ok
2021-08-01 teensy code
2021-08-01 v161
2021-08-04 added CheckBumpers on PeriOutStop
2021-08-04 correction on previous change
2021-08-04 made equal
2021-08-04 revertedShowMessageLn
2021-08-05 no dht setup when not in use
2021-08-05 simple return if not dht22use
2021-08-05 no MC33926 on RL1000
2021-08-05 Update robot.cpp
    RonPeeters request : Bumper check while peri_out_stop
2021-08-06 PDF update
2021-08-08 teensy_pcb
2021-08-09 remove big file
2021-08-09 remove teensy part
2021-08-27 stationHeading
2021-09-09 chargesense
    bug detected by sefanH
2021-09-11 pwm motor frequency
2021-09-12 new motor finish
    on slope when motor stop the odometry can go reverse and it's generate a pause on the movement until timeout
2021-09-12 end lane state
    new state at the max lane lenght to avoid reverse
2021-09-12 corner
    corner detection was not on this code ,only into rl1000
2021-09-12 mowpattern change on roll to inside
2021-09-18 station and imu
2021-09-23 Add console over WIFI
    Console fail over WIFI
2021-09-26 ESP32 WIFI Arduremote
2021-09-29 autostart
    add the possbility to stop the sender out A if mower is not in station but mow in area2 out B of the same sender
2021-09-29 Test if sender is OK
2021-09-29 check signal
2021-09-30 sender non auto stop
2021-09-30 version nr
2021-10-21 noise mesure in pfod
2021-10-23 rfidlist ok
2021-10-25 pfod rfid work
2021-10-30 rfid pfod
2021-11-01 rfid list pfod
2021-11-13 name rfid
2021-12-05 rfid
2021-12-11 mqtt without pi
    RFID and Mqtt version for use without raspberry pi
2021-12-12 mqtt add
2022-01-24 vision data
2022-02-03 esp32/rfid/mqtt
2022-03-15 test for statio heading
2022-03-18 new version
    new version
2022-03-22 escape_corner
2022-03-27 small improve
2022-03-27 text
2022-04-01 Update robot.cpp
    station heading not always OK when start
2022-04-01 Update robot.cpp
    duplicate message
2022-04-02 manual_drive_cleanning
2022-04-03 station heading
2022-04-09 Update robot.cpp
    start button in station mow motor not started
2022-04-15 Update robot.cpp
    motormowpwm coeff
    to 0.8
2022-04-27 web server
2022-04-27 speed
2022-04-27 perimeter menu split
2022-04-28 1.85 vers
2022-04-28 Ruppet
    Last FR version
2022-04-30 bt speed
2022-05-03 gps work
    Not yet finish
2022-05-03 web control furst Ruprecht
    not finish
2022-05-08 webserver
2022-05-09 ver bb2
2022-05-10 minor change
    web serveur console
2022-05-11 timer
    start wire by timer
2022-05-12 pfod
    Universal pfod firt test
2022-05-19 heading issue
    https://forum.ardumower.de/threads/wiremowing-doesnt-work.24763/#post-53481
2022-05-27 Update pfod.cpp
    bug on docking speed
2023-02-10 add 3d file
2023-02-12 home assistant config
2025-01-15 Update mower.h
    remove pi console support
2025-01-15 esp32 serial2
    isuue on new arduino ide version serial2 and esp32
2025-04-02 ngp_not_ok
